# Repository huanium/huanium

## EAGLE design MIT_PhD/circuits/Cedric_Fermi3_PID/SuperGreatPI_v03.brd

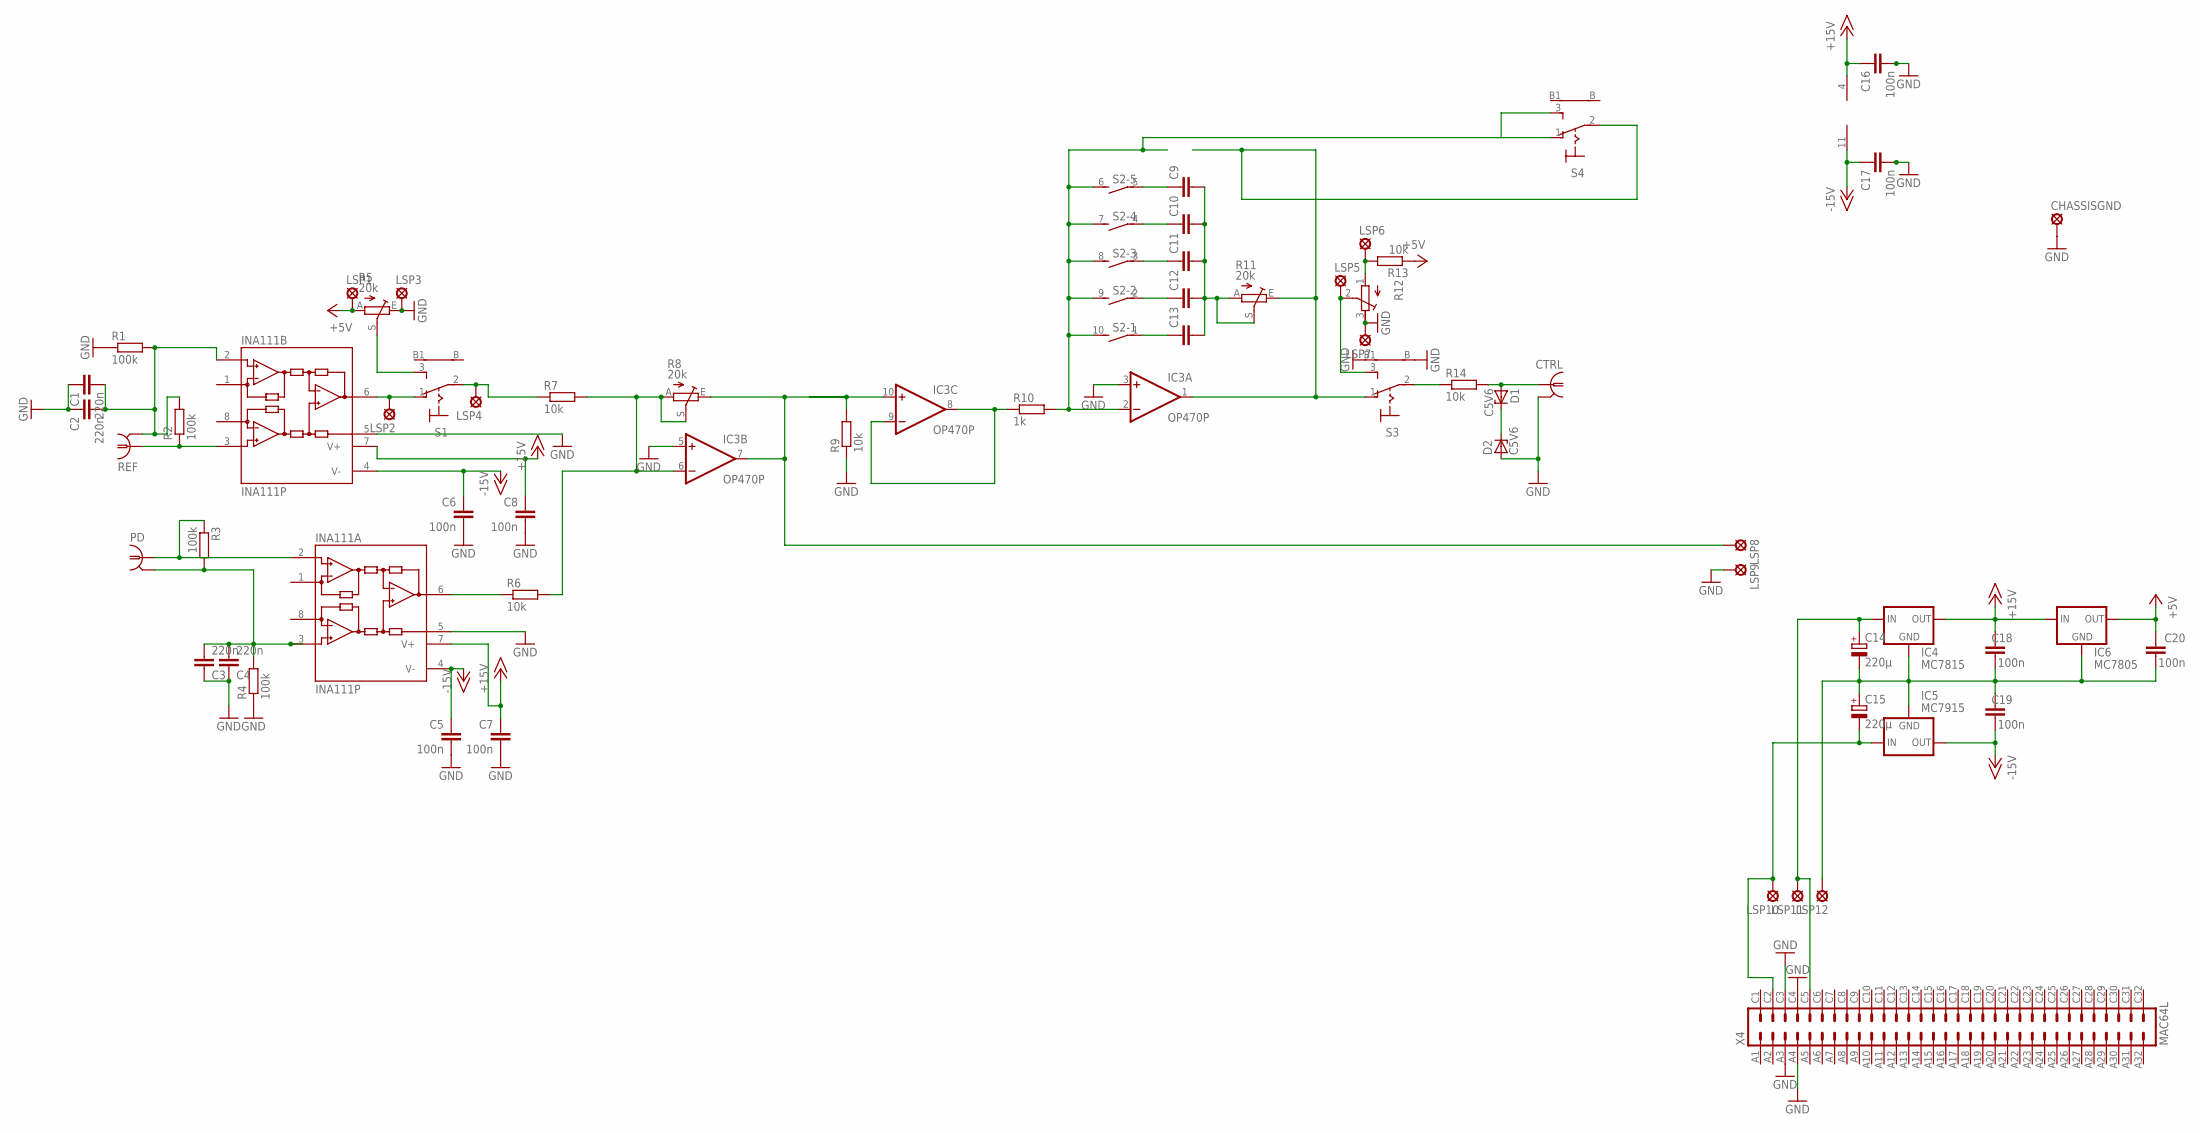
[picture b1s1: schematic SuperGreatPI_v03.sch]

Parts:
C1, C2, C3, C4: 220n; C025-024X044
C5, C6, C7, C8, C16, C17, C18, C19, C20: 100n; C025-024X044
C9, C10, C11, C12, C13: C-EU050-025X075; C050-025X075
C14, C15: 220µ; E3,5-8
CHASSISGND: MCS08
CTRL: 1-227161-0; AMP_227161
D1, D2: C5V6; DO34Z7
IC3: OP470P; DIL14
IC4: MC7815; 78XXS
IC5: MC7915; 79XXS
IC6: MC7805; 78XXS
INA111A, INA111B: INA111P; DIL08
LSP1, LSP2, LSP3, LSP4, LSP5, LSP6, LSP7, LSP8, LSP9: MCS08
LSP10, LSP11: -18V; MCS08
LSP12: GND; MCS08
PD: 1-227161-0; AMP_227161
R1, R2, R3, R4: 100k; 0207/2V
R5, R8, R11: 20k; PT-SPIN
R6, R7, R9, R13, R14: 10k; 0207/10
R10: 1k; 0207/10
R12: R-TRIMM3299W; RTRIM3299W
REF: 1-227161-0; AMP_227161
S1, S3, S4: LPV-1
S2: DS05E; DS-05
X4: MAC64L

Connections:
+5V: C20.1, IC6.OUT, LSP1.MP, R5.A, R13.1
+15V: C7.1, C8.1, C16.1, C18.1, IC3.4 (V+), IC4.OUT, IC6.IN, INA111A.7 (V+), INA111B.7 (V+)
-15V: C5.1, C6.1, C17.1, C19.2, IC3.11 (V-), IC5.OUT, INA111A.4 (V-), INA111B.4 (V-)
GND: C1.1, C2.1, C3.1, C4.1, C5.2, C6.2, C7.2, C8.2, C14.-, C15.+, C16.2, C17.2, C18.2, C19.1, C20.2, CHASSISGND.MP, CTRL.2 (GND), D2.A, IC3.3 (+IN), IC3.5 (+IN), IC4.GND, IC5.GND, IC6.GND, INA111A.5 (REF), INA111B.5 (REF), LSP3.MP, LSP7.MP, LSP9.MP, LSP12.MP, R1.1, R4.1, R5.E, R9.1, R12.3 (E), S3.B, S3.B1, X4.A3, X4.A4, X4.C3, X4.C4
unnamed: IC3.8 (OUT), IC3.9 (-IN), R10.1
unnamed: INA111A.6 (OUT), R6.1
unnamed: INA111B.3 (+IN), R2.1, REF.1
unnamed: INA111A.2 (-IN), PD.1, R3.1
unnamed: C1.2, C2.2, INA111B.2 (-IN), R1.2, R2.2, REF.2 (GND)
unnamed: C3.2, C4.2, INA111A.3 (+IN), PD.2 (GND), R3.2, R4.2
unnamed: C14.+, IC4.IN, LSP11.MP, X4.C5
unnamed: IC3.7 (OUT), IC3.10 (+IN), LSP8.MP, R8.E, R9.2
unnamed: CTRL.1, D1.A, R14.2
unnamed: IC3.2 (-IN), R10.2, S2.6 (2), S2.7 (2), S2.8 (2), S2.9 (2), S2.10 (2), S4.1 (O), S4.3 (S)
unnamed: C15.-, IC5.IN, LSP10.MP, X4.C2
unnamed: C9.2, C10.2, C11.2, C12.2, C13.2, R11.A, R11.S
unnamed: LSP4.MP, R7.1, S1.2
unnamed: IC3.1 (OUT), R11.E, S3.1 (O), S4.2
unnamed: IC3.6 (-IN), R6.2, R7.2, R8.A, R8.S
unnamed: R5.S, S1.3 (S)
unnamed: C9.1, S2.5 (1)
unnamed: C10.1, S2.4 (1)
unnamed: C11.1, S2.3 (1)
unnamed: C12.1, S2.2 (1)
unnamed: C13.1, S2.1
unnamed: INA111B.6 (OUT), LSP2.MP, S1.1 (O)
unnamed: LSP6.MP, R12.1 (A), R13.2
unnamed: R14.1, S3.2
unnamed: LSP5.MP, R12.2 (S), S3.3 (S)
unnamed: D1.C, D2.C

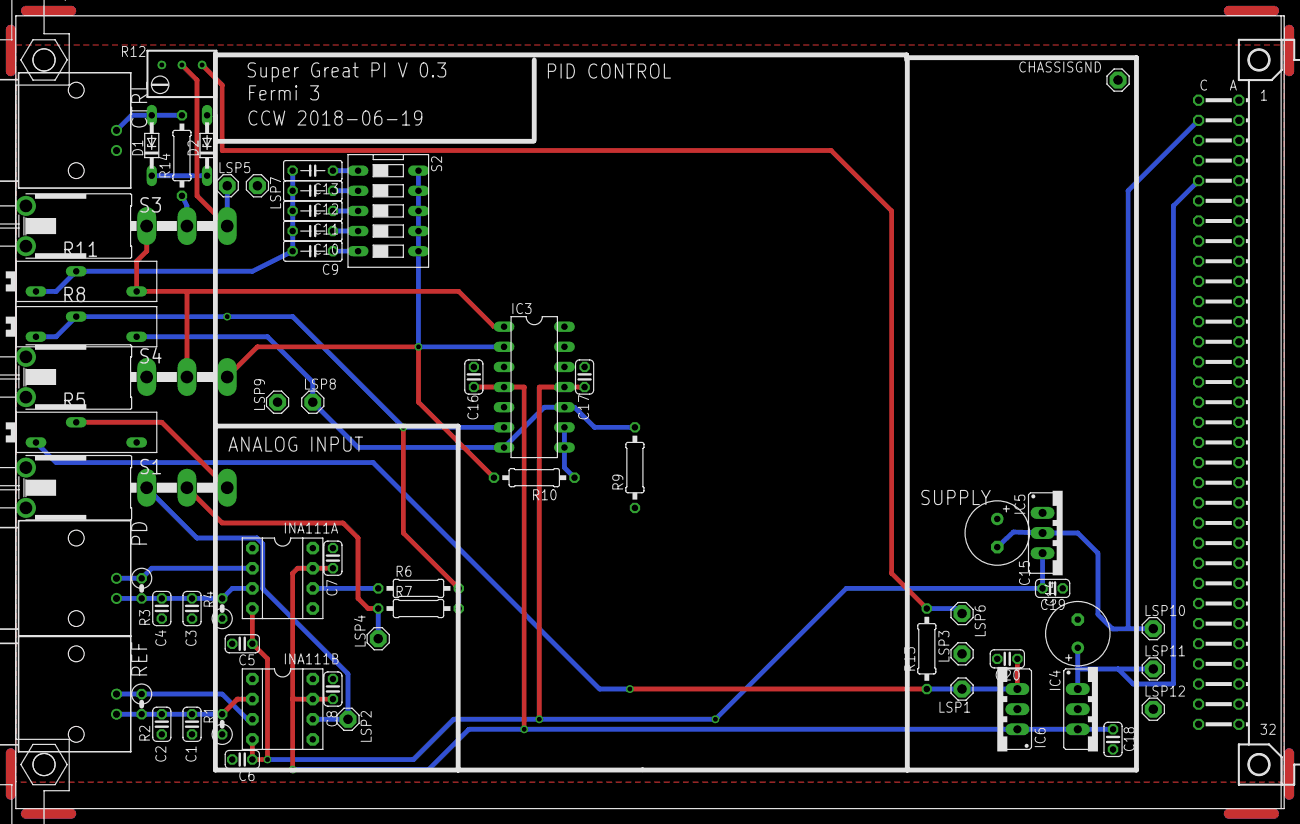
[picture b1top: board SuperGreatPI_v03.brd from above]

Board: 2 copper layers, 160.0 x 100.0 mm, 64 parts (0 on the bottom side), 30 nets.

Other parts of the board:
U$1: EK-FP

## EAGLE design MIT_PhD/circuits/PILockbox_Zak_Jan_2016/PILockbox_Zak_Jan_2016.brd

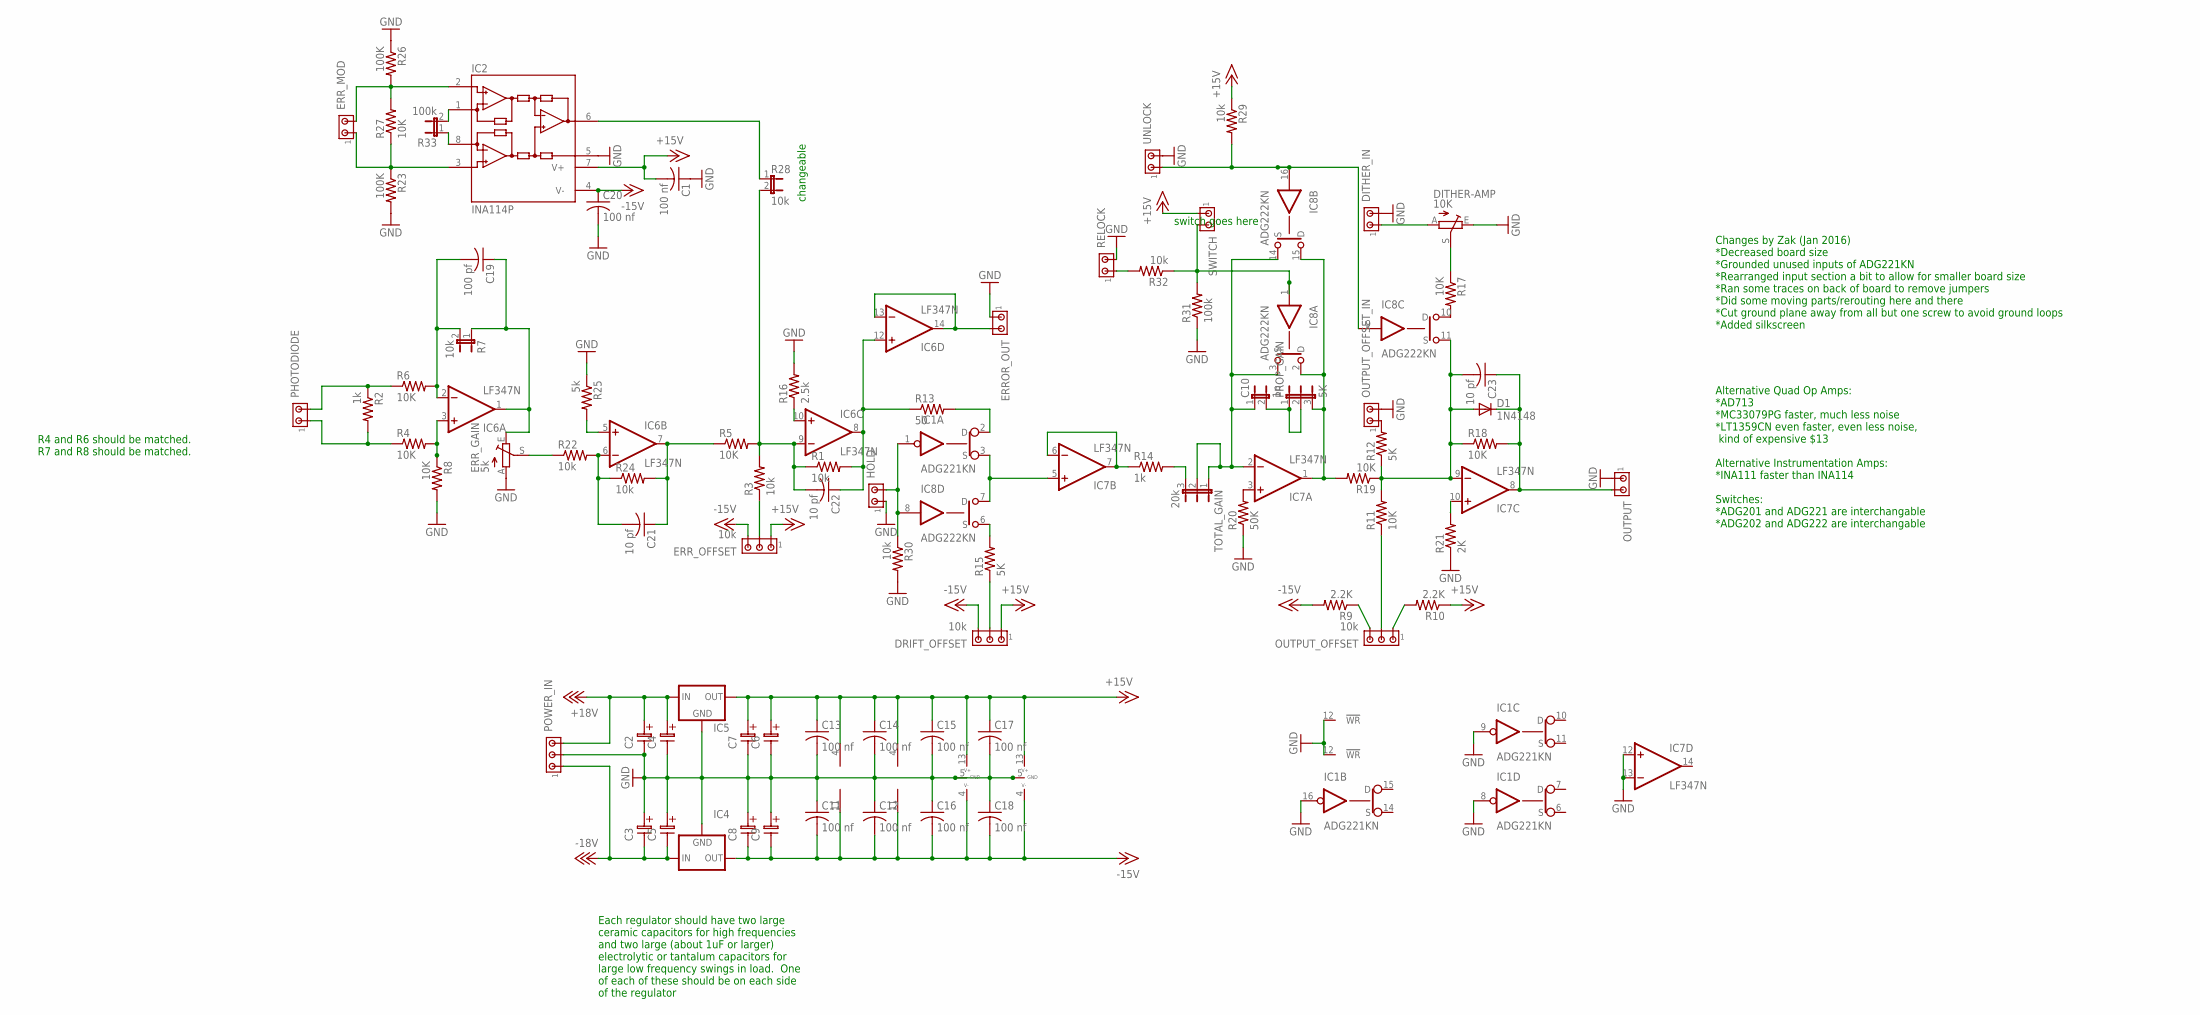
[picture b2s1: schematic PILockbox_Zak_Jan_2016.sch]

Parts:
C1, C11, C12, C13, C14, C15, C16, C17, C18, C20: 100 nf; C0805
C2, C3, C4, C5, C6, C7, C8, C9: ELC-2,5; ES-2,5
C10: 1n; JP1
C19: 100 pf; C0805
C21, C22, C23: 10 pf; C0805
D1: 1N4148; DO35-10
DITHER-AMP: 10K; RJ9W
DITHER_IN: MTA02-100; 10X02MTA
DRIFT_OFFSET: 10k; 10X03MTA
ERROR_OUT: MTA02-100; 10X02MTA
ERR_GAIN: 5k; RJ9W
ERR_MOD: MTA02-100; 10X02MTA
ERR_OFFSET: 10k; 10X03MTA
HOLD: MTA02-100; 10X02MTA
IC1: ADG221KN; DIL16
IC2: INA114P; DIL08
IC4: 79XXL
IC5: 78XXL
IC6, IC7: LF347N; DIL14
IC8: ADG222KN; DIL16
OUTPUT: MTA02-100; 10X02MTA
OUTPUT_OFFSET: 10k; 10X03MTA
OUTPUT_OFFSET_IN: MTA02-100; 10X02MTA
PHOTODIODE: MTA02-100; 10X02MTA
POWER_IN: MTA03-100; 10X03MTA
PROP_GAIN: 5K; JP2
R1, R3, R22, R24, R29, R30, R32: 10k; R1206
R2, R14: 1k; R1206
R4, R5, R6, R8, R11, R17, R18, R19, R27: 10K; R1206
R7, R28: 10k; JP1
R9, R10: 2.2K; R1206
R12, R15: 5K; R1206
R13: 50; R1206
R16: 2.5k; R1206
R20: 50K; R1206
R21: 2K; R1206
R23, R26: 100K; R1206
R25: 5k; R1206
R31: 100k; R1206
R33: 100k; JP1
RELOCK: MTA02-100; 10X02MTA
SWITCH: MTA02-100; 10X02MTA
TOTAL_GAIN: 20k; JP2
UNLOCK: MTA02-100; 10X02MTA

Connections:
+15V: C1.2, C6.1, C7.1, C13.1, C14.1, C15.1, C17.1, DRIFT_OFFSET.1, ERR_OFFSET.1, IC1.13 (V+), IC2.7 (V+), IC5.OUT, IC6.4 (V+), IC7.4 (V+), IC8.13 (V+), R10.1, R29.1, SWITCH.1
+18V: C2.1, C4.1, IC5.IN, POWER_IN.3
-15V: C8.2, C9.2, C11.2, C12.2, C16.2, C18.2, C20.1, DRIFT_OFFSET.3, ERR_OFFSET.3, IC1.4 (V-), IC2.4 (V-), IC4.OUT, IC6.11 (V-), IC7.11 (V-), IC8.4 (V-), R9.2
-18V: C3.2, C5.2, IC4.IN, POWER_IN.1
GND: C1.1, C2.2, C3.1, C4.2, C5.1, C6.2, C7.2, C8.1, C9.1, C11.1, C12.1, C13.2, C14.2, C15.2, C16.1, C17.2, C18.1, C20.2, DITHER-AMP.E, DITHER_IN.2, ERROR_OUT.1, ERR_GAIN.A, HOLD.1, IC1.5 (GND), IC1.8 (IN), IC1.9 (IN), IC1.12 (!WR), IC1.16 (IN), IC2.5 (REF), IC4.GND, IC5.GND, IC7.12 (+IN), IC7.13 (-IN), IC8.5 (GND), IC8.12 (!WR), OUTPUT.1, OUTPUT_OFFSET_IN.2, POWER_IN.2, R8.2, R16.2, R20.1, R21.1, R23.2, R25.1, R26.1, R30.2, R31.1, RELOCK.2, UNLOCK.2
unnamed: IC6.3 (+IN), R4.2, R8.1
unnamed: C19.2, IC6.2 (-IN), R6.2, R7.2
unnamed: IC6.10 (+IN), R16.1
unnamed: ERROR_OUT.2, IC6.13 (-IN), IC6.14 (OUT)
unnamed: PHOTODIODE.2, R2.1, R6.1
unnamed: PHOTODIODE.1, R2.2, R4.1
unnamed: C19.1, ERR_GAIN.E, IC6.1 (OUT), R7.1
unnamed: IC1.3 (S), IC7.5 (+IN), IC8.7 (D)
unnamed: C22.2, IC6.9 (-IN), R1.1, R3.2, R5.2, R28.2
unnamed: ERR_OFFSET.2, R3.1
unnamed: C22.1, IC6.8 (OUT), IC6.12 (+IN), R1.2, R13.1
unnamed: IC1.2 (D), R13.2
unnamed: HOLD.2, IC1.1 (IN), IC8.8 (IN), R30.1
unnamed: DRIFT_OFFSET.2, R15.1
unnamed: IC8.6 (S), R15.2
unnamed: IC7.6 (-IN), IC7.7 (OUT), R14.1
unnamed: R14.2, TOTAL_GAIN.3
unnamed: C10.1, IC7.2 (-IN), IC8.3 (S), IC8.14 (S), TOTAL_GAIN.1, TOTAL_GAIN.2
unnamed: IC7.3 (+IN), R20.2
unnamed: C10.2, PROP_GAIN.1, PROP_GAIN.2
unnamed: IC7.1 (OUT), IC8.2 (D), IC8.15 (D), PROP_GAIN.3, R19.2
unnamed: IC8.9 (IN), IC8.16 (IN), R29.2, UNLOCK.1
unnamed: IC8.1 (IN), R31.2, R32.1, SWITCH.2
unnamed: C23.2, D1.A, IC7.9 (-IN), IC8.11 (S), R11.2, R12.1, R18.1, R19.1
unnamed: OUTPUT_OFFSET.3, R9.1
unnamed: OUTPUT_OFFSET.1, R10.2
unnamed: OUTPUT_OFFSET.2, R11.1
unnamed: OUTPUT_OFFSET_IN.1, R12.2
unnamed: DITHER-AMP.A, DITHER_IN.1
unnamed: IC2.6 (OUT), R28.1
unnamed: IC8.10 (D), R17.2
unnamed: IC7.10 (+IN), R21.2
unnamed: ERR_MOD.2, IC2.2 (-IN), R26.2, R27.2
unnamed: C23.1, D1.C, IC7.8 (OUT), OUTPUT.2, R18.2
unnamed: ERR_MOD.1, IC2.3 (+IN), R23.1, R27.1
unnamed: ERR_GAIN.S, R22.1
unnamed: C21.1, IC6.7 (OUT), R5.1, R24.2
unnamed: C21.2, IC6.6 (-IN), R22.2, R24.1
unnamed: IC6.5 (+IN), R25.2
unnamed: R32.2, RELOCK.1
unnamed: DITHER-AMP.S, R17.1
unnamed: IC2.1 (RG), R33.2
unnamed: IC2.8 (RG), R33.1

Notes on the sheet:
changeable
switch goes here
Changes by Zak (Jan 2016) *Decreased board size *Grounded unused inputs of ADG221KN *Rearranged input section a bit to allow for smaller board size *Ran some traces on back of board to remove jumpers *Did some moving parts/rerouting here and there *Cut ground plane away from all but one screw to av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
R4 and R6 should be matched. R7 and R8 should be matched.
Alternative Quad Op Amps: *AD713 *MC33079PG faster, much less noise *LT1359CN even faster, even less noise, kind of expensive $13 Alternative Instrumentation Amps: *INA111 faster than INA114 Switches: *ADG201 and ADG221 are interchangable *ADG202 and ADG222 are interchangable
Each regulator should have two large ceramic capacitors for high frequencies and two large (about 1uF or larger) electrolytic or tantalum capacitors for large low frequency swings in load. One of each of these should be on each side of the regulator

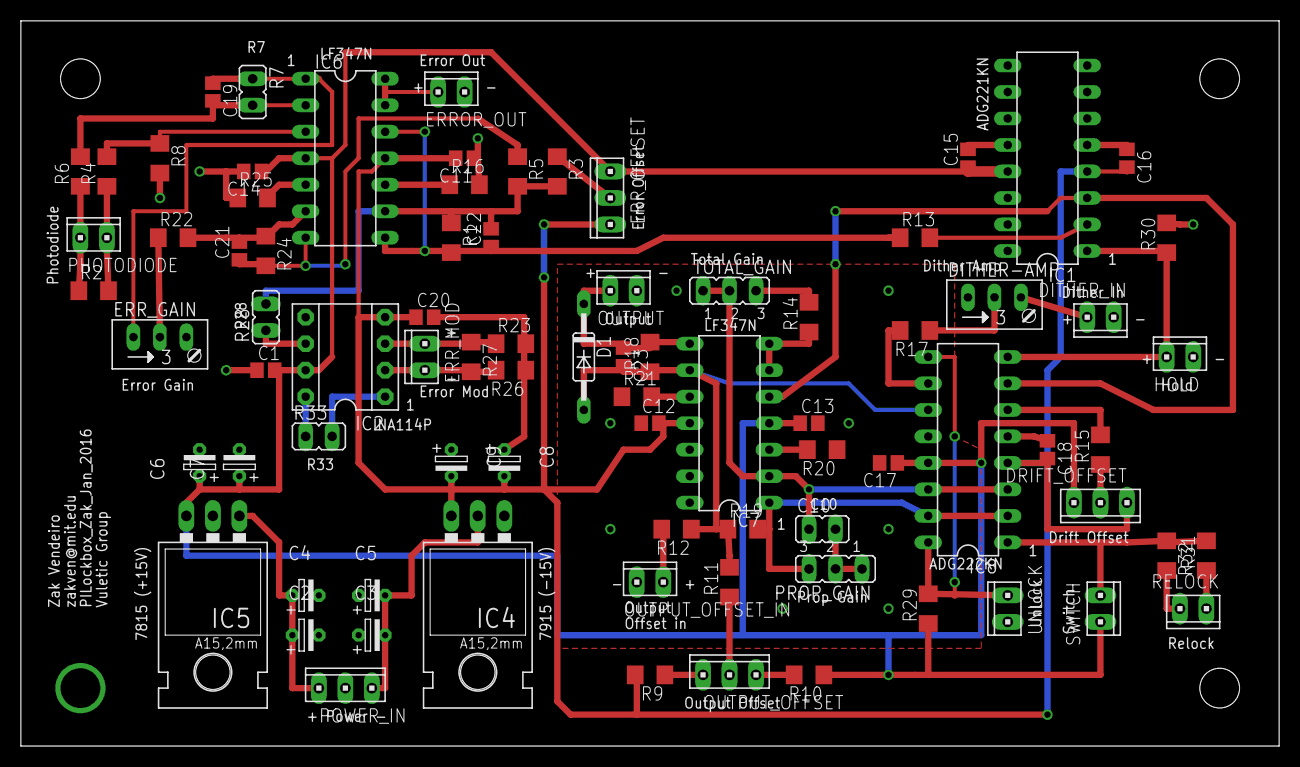
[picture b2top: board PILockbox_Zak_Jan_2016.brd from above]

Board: 2 copper layers, 120.6 x 69.5 mm, 82 parts (0 on the bottom side), 48 nets.

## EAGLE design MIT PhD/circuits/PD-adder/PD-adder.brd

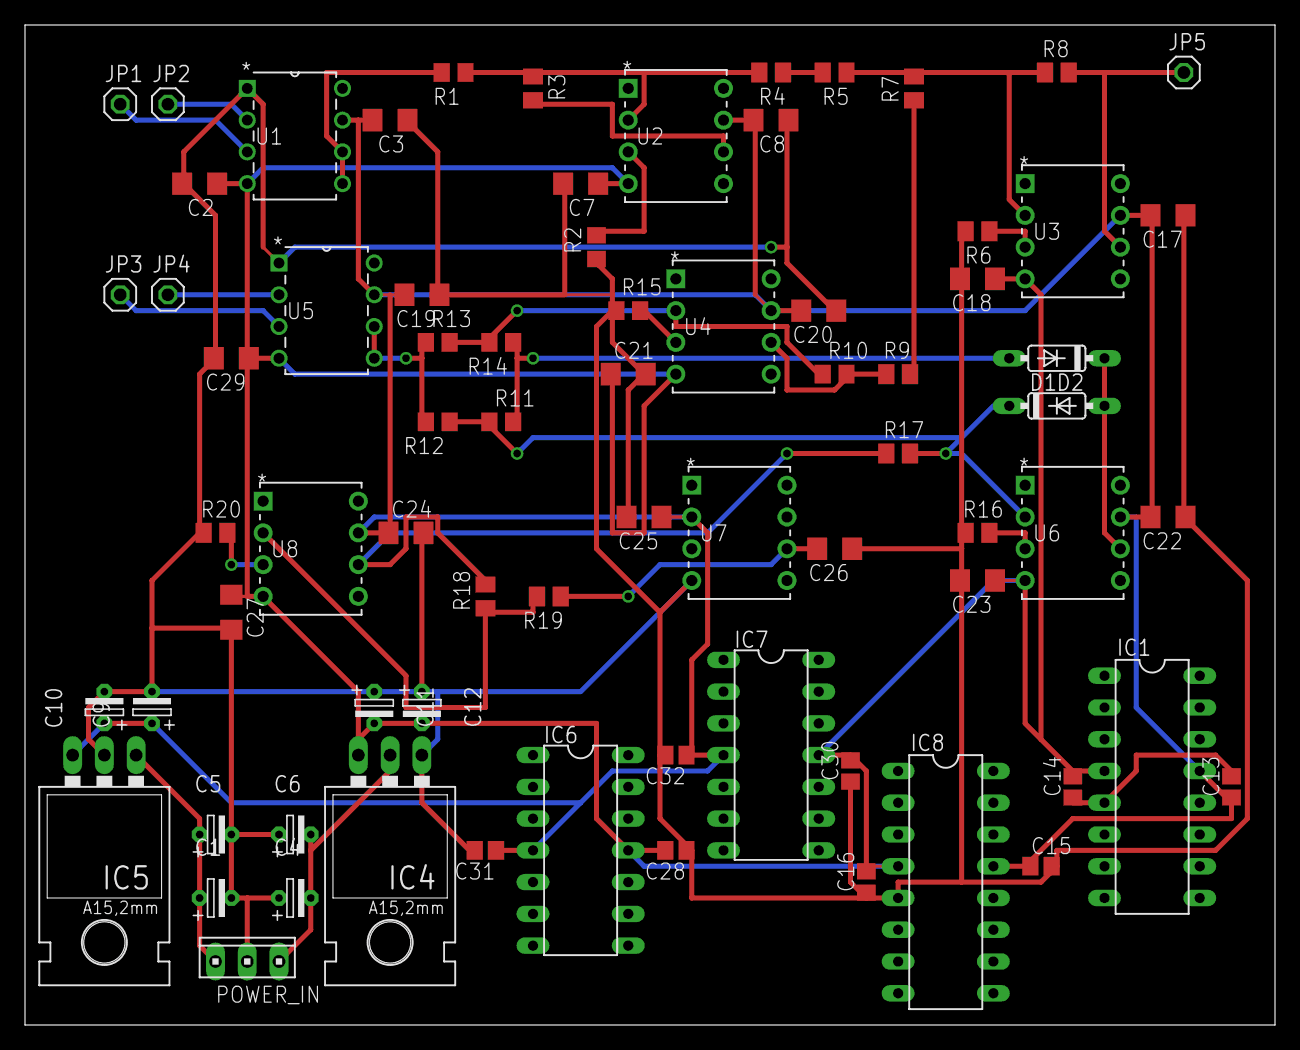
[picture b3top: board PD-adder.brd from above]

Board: 2 copper layers, 100.0 x 80.0 mm, 74 parts (0 on the bottom side), 31 nets.

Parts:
C1, C4, C5, C6, C9, C10, C11, C12: 1uF; ES-2,5
C2, C3, C7, C8, C17, C19, C20, C21, C22, C23, C24, C25, C27, C29: 100nF; C1206@1
C13, C14, C15, C16, C28, C30, C31, C32: 100nF; C0805
C18: C1206@1
C26: 10uF; C1206@1
D1, D2: 1N4148DO35-7; DO35-7
IC1: ADG221KN; DIL16
IC4: 79XXL
IC5: 78XXL
IC6, IC7: LF347N; DIL14
IC8: ADG222KN; DIL16
JP1, JP2, JP3, JP4, JP5: 1X01
POWER_IN: 10X03MTA
R1, R10, R11, R12, R13, R14: 680; R0805
R2, R15: 330; R0805
R3, R4, R5, R7, R8, R9, R17, R18, R19: 680; M0805
R6, R16, R20: 330; M0805
U1, U5: INA105KP; P8
U2, U3, U4, U6, U8: OP27EZ; Q_8_ADI
U7: REF01EZ; Q_8_ADI

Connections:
+15V: C3.2, C8.2, C9.1, C10.1, C13.1, C15.1, C17.2, C19.2, C20.2, C22.2, C24.1, C25.1, C31.1, C32.1, IC1.13, IC5.OUT, IC6.4, IC7.4, IC8.13, U1.7, U2.7, U3.7, U4.7, U5.7, U6.7, U7.2, U8.7
+18V: C1.1, C5.1, IC5.IN, POWER_IN.3
-15V: C2.1, C7.1, C11.2, C12.2, C14.2, C16.2, C18.1, C21.1, C23.1, C27.1, C28.2, C29.1, C30.2, IC1.4, IC4.OUT, IC6.11, IC7.11, IC8.4, U1.4, U2.4, U3.4, U4.4, U5.4, U6.4, U8.4
-18V: C4.2, C6.2, IC4.IN, POWER_IN.1
GND: C1.2, C2.2, C3.1, C4.1, C5.2, C6.1, C7.2, C8.1, C9.2, C10.2, C11.1, C12.1, C15.2, C16.1, C17.1, C18.2, C19.1, C20.1, C21.2, C22.1, C23.2, C24.2, C25.2, C26.1, C27.2, C28.1, C29.2, C30.1, C31.2, C32.2, IC4.GND, IC5.GND, IC8.5, POWER_IN.2, R2.1, R6.2, R15.1, R16.1, R20.1, U1.1, U5.1, U7.4
unnamed: C13.2, C14.1, IC1.5
unnamed: R2.2, U2.3
unnamed: R3.2, U2.6
unnamed: R4.1, R5.2
unnamed: R5.1, R7.2, R8.1, U3.2
unnamed: R7.1, R9.2
unnamed: R9.1, R10.2, U4.6
unnamed: R10.1, R13.2, R14.2, U4.2
unnamed: R15.2, U4.3
unnamed: D2.A, R11.2, R14.1
unnamed: R12.2, R13.1, U5.5, U5.6
unnamed: D1.C, R11.1, R12.1, R17.2, U6.2
unnamed: R16.2, U6.3
unnamed: R20.2, U8.3
unnamed: R1.1, R3.1, R4.2, U2.2
unnamed: R6.1, U3.3
unnamed: R17.1, R18.2, U8.6
unnamed: D1.A, D2.C, U6.6
unnamed: R18.1, R19.2, U8.2
unnamed: C26.2, R19.1, U7.6
VHI-IN+: JP1.1, U1.3
VHI-IN-: JP2.1, U1.2
VLO-IN+: JP3.1, U5.3
VLO-IN-: JP4.1, U5.2
VOUT: R1.2, U1.5, U1.6
V_OUT: JP5.1, R8.2, U3.6

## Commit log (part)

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2021-08-29 Li laser table diagram
2021-08-30 convolution power stuff
2021-08-31 Li laser table updates
2021-09-01 li table updates
2021-09-01 li updates
2021-09-02 laser table updates and archives.html
2021-09-08 organizations
2021-09-09 file updates
2021-09-15 psets
2021-10-18 psets and notes
2021-10-19 research
2021-10-20 bec1
2021-10-20 psets+BEC1
2021-10-21 becs
2021-10-29 test prep
2021-10-31 notes
2021-11-04 failures
2021-11-10 pset
2021-11-16 notes and psets
2021-12-06 conv powers
2021-12-20 psets n tests
2022-01-22 imaging software migration to APPDESIGNER
2022-04-09 stuff
2022-04-09 test
2022-04-11 injection locker
2022-04-12 injection locker and files
2022-04-12 rearrange
2022-04-12 fsdfd
2022-04-15 injecion locker
2022-04-25 injection locker and term paper
2022-04-27 references
2022-04-28 paper
2022-04-30 files
2022-05-03 writing
2022-05-07 term paper
2022-05-19 bec1 software
2022-05-19 software
2022-05-24 BEC1 poster stuff
2022-05-25 BEC1 poster
2022-05-26 BEC1 poster TeX
2022-05-26 BEC1 DAMOP22 poster
2022-06-16 BEC1 software Top
2022-06-17 BEC1 image browser
2022-06-17 BEC1 image viewer
2022-06-27 BEC1 img
2022-07-01 NEC1 image viewer
2022-07-30 new machine
2022-08-01 BEC1 and quals
2022-08-01 quals
2022-08-01 quals prep
2022-08-04 oral qual prep
2022-08-19 ZGS slides
2022-08-28 image_browser upgrade
2022-08-28 Bump numpy in /MIT PhD/BEC1/Software/Image_Browser/satyendra
    Bumps [numpy](https://github.com/numpy/numpy) from 1.21.6 to 1.22.0.
    - [Release notes](https://github.com/numpy/numpy/releases)
    - [Changelog](https://github.com/numpy/numpy/blob/main/doc/RELEASE_WALKTHROUGH.rst)
    - [Commits](https://github.com/numpy/numpy/compare/v1.21.6...v1.22.0)
    ---
    updated-dependencies:
2022-08-28 Bump numpy
    Bumps [numpy](https://github.com/numpy/numpy) from 1.18.1 to 1.22.0.
    - [Release notes](https://github.com/numpy/numpy/releases)
    - [Changelog](https://github.com/numpy/numpy/blob/main/doc/HOWTO_RELEASE.rst)
    - [Commits](https://github.com/numpy/numpy/compare/v1.18.1...v1.22.0)
    ---
    updated-dependencies:
2022-08-28 Bump numpy in /MIT_PhD/BEC1/Software/Image_Browser/satyendra
    Bumps [numpy](https://github.com/numpy/numpy) from 1.21.6 to 1.22.0.
    - [Release notes](https://github.com/numpy/numpy/releases)
    - [Changelog](https://github.com/numpy/numpy/blob/main/doc/RELEASE_WALKTHROUGH.rst)
    - [Commits](https://github.com/numpy/numpy/compare/v1.21.6...v1.22.0)
    ---
    updated-dependencies:
2022-08-31 reorganize
2022-09-08 BEC1 stuff
2022-09-16 QC pset1
2022-09-17 injection locker serial
2022-09-17 qc-bec1
2022-09-21 study
2022-09-28 qc and zgs
2022-09-30 image viewer
2022-09-30 Bump numpy in /MIT_PhD/BEC1/Software/Image_Browser_with_Saver/satyendra
    Bumps [numpy](https://github.com/numpy/numpy) from 1.21.6 to 1.22.0.
    - [Release notes](https://github.com/numpy/numpy/releases)
    - [Changelog](https://github.com/numpy/numpy/blob/main/doc/RELEASE_WALKTHROUGH.rst)
    - [Commits](https://github.com/numpy/numpy/compare/v1.21.6...v1.22.0)
    ---
    updated-dependencies:
2022-10-01 mac setup test
2022-10-05 papers
2022-10-07 portal
2022-10-17 mask
2022-10-18 physics
2022-10-20 fermi
2022-10-20 docs
2022-10-23 image browser
2022-11-03 blah
2022-11-03 BEC fitting
2022-11-06 image viewer with BEC analysis
2022-11-11 image browser:
2022-11-17 injection monitor with python
2022-11-22 masks
2022-11-22 Bump pillow in /MIT_PhD/BEC1/Software/Image_Browser_with_Saver/satyendra
    Bumps [pillow](https://github.com/python-pillow/Pillow) from 9.0.1 to 9.3.0.
    - [Release notes](https://github.com/python-pillow/Pillow/releases)
    - [Changelog](https://github.com/python-pillow/Pillow/blob/main/CHANGES.rst)
    - [Commits](https://github.com/python-pillow/Pillow/compare/9.0.1...9.3.0)
    ---
    updated-dependencies:
2022-12-09 Bump certifi
    Bumps [certifi](https://github.com/certifi/python-certifi) from 2021.10.8 to 2022.12.7.
    - [Release notes](https://github.com/certifi/python-certifi/releases)
    - [Commits](https://github.com/certifi/python-certifi/compare/2021.10.08...2022.12.07)
    ---
    updated-dependencies:
    - dependency-name: certifi
2022-12-22 image browser python
2023-01-13 poster
2023-01-30 posters
2023-01-31 AMO formulas
2023-01-31 formulas
2023-01-31 amo notebook
2023-02-07 class materials
2023-02-07 AMO 1 notebook
2023-02-09 amo notebook 1 updates
2023-02-09 hqb analysis
2023-02-10 bec1 calculator
2023-02-20 bec1 and amo stuff
2023-02-21 amo2
2023-02-24 bec1 calc
2023-03-07 amo2 pset4
2023-04-11 pset8
2023-04-30 bec1 to fermi1
2023-05-04 amo 2
2023-05-05 fermi1 calculator
2023-05-08 amo2 term paper
2023-05-11 amo 2 term paper
2023-05-16 AMO_Calculator
2023-05-21 term paper and antenna stuff
2023-05-21 fermi1 antenna design RWA v1 ansys
2023-05-22 antenna updates
2023-05-25 numerov_cooley
2023-05-28 amo calc
2023-05-30 amo calc nak
2023-06-22 amo calculator
2023-07-28 hfs amo calulator
2023-08-11 EOM and rf source
2023-10-22 Fermi1 analysis code development 1
2023-10-23 Fermi1 analysis code development 2
2023-10-27 Fermi1 analysis code development 3
2023-12-13 AMO calculator updates
2024-02-11 Feb 11 2024
2024-02-12 more molecules
2024-02-27 Green's function notes
2024-06-11 lineshapes
2024-06-24 small updates
2024-06-27 spectral functions
2025-01-24 fermi1 calc 4
2025-02-12 lattice images

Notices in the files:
parts and their libraries:
COPYRIGHT: Copyright (C) 2021 Ultra Librarian. All rights reserved.
